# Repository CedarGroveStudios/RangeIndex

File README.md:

# Range_Slicer
## cedargrove_range_slicer
A CircuitPython class for scaling a range of input values into indexed/quantized output values. Adjustable output slice hysteresis is used to provide dead-zone squelching.

[Conceptual Methodology (animation)](https://youtu.be/ndU70NTm_Bk)

Range_Slicer is a general-purpose analog value converter that linearly scales the input then quantizes it into a collection of precise output slice values. The class detects input value changes and applies selectable hysteresis when slice edge thresholds are reached to eliminate dead-zone noise issues. Applications include converting rotary knob position to discrete ranges of MIDI values, analog signal noise processing, level detection, and signal display.

### Implementation Notes

See use example code in the _examples_ folder.

#### Software and Dependencies:
•	Adafruit CircuitPython firmware for the supported boards: https://github.com/adafruit/circuitpython/releases

#### ```class cedargrove_range_slicer.Slicer(*, in_min=0, in_max=65535, out_min=0, out_max=65535, slice=1.0, hyst_factor=0.10, out_integer=False, debug=False)```

Class representing the CedarGroveMaker Range_Slicer.

Parameters:	

-	`in_min` – The input range minimum. Can be any positive or negative value, smaller or larger than the input range maximum. Input range minimum and maximum values cannot be equal. Defaults to `0`.

-	`in_max` – The input range maximum. Can be any positive or negative value, smaller or larger than the input range minimum. Input range minimum and maximum values cannot be equal. Defaults to `65535`.

-	`out_min` – The output index minimum. Can be any positive or negative value, smaller or larger than the output index maximum. Output index minimum and maximum values cannot be equal. Defaults to `0`.

-	`out_max` – The output index maximum. Can be any positive or negative value, smaller or larger than the output index minimum. Output index minimum and maximum values cannot be equal. Defaults to `65535`.

-	`slice` – The size of an output index slice. Can be any positive or negative value other than zero. Defaults to `1.0`.

-	`hyst_factor` – The size of the hysteresis threshold expressed as a factor of the slice size. Can be a positive value from 0 to 1.0. Defaults to `0.10` (10% of the slice size value).

- `out_integer` - Truncates the output value to an integer data type. Defaults to False (floating data type).

-	`debug` – Turn on debug printout. Defaults to `False`.

#### `range_slicer(input=0)`

Applies the slicer algorithm to an input value using the initialization parameters. Returns 1) the output index floating point value (default) or optionally truncated integer value and 2) a flag that is set to `True` when the output value is not equal to the previous result. This is the primary function of the Range_Slicer class.

Parameters:	

- `input` – The input value to convert. Can be any positive or negative numeric value. Defaults to `0`.

#### `range_min(in_min=0)` 

Changes the default range (input) minimum to a new value.

Parameters:	

- `in_min` – The input range minimum. Can be any positive or negative value, smaller or larger than the input range maximum. Input range minimum and maximum values cannot be equal. Defaults to `0`.

#### `range_max(in_max=65535)` 

Changes the default range (input) maximum to a new value.

Parameters:	

- `in_max` – The input range maximum. Can be any positive or negative value, smaller or larger than the input range minimum. Input range minimum and maximum values cannot be equal. Defaults to `65535`.

#### `index_min(out_min=0)` 

Changes the default index (output) minimum to a new value.

Parameters:	

- `out_min` – The index output minimum. Can be any positive or negative value, smaller or larger than the output index maximum. Output index minimum and maximum values cannot be equal. Defaults to `0`.

#### `index_max(out_max=65535)` 

Changes the default index (output) maximum to a new value.

Parameters:	

- `out_max` – The output index maximum. Can be any positive or negative value, smaller or larger than the output index minimum. Output index minimum and maximum values cannot be equal. Defaults to `65535`.

#### `slice(size=1.0)` 

Changes the default slice size to a new value.

Parameters:	

- `size` – The size of an index output slice. Can be any positive or negative value other than zero. Defaults to `1.0`.

#### `hysteresis(hyst_factor=0.10)`

Changes the default hysteresis threshold to a new value.

Parameters:	

- `hyst_factor` – The size of the hysteresis threshold expressed as a factor of the slice size. Can be a positive value from 0 to 1.0. Defaults to `0.10` (10% of the slice size value).

#### `index_type(out_integer=False)`

Changes the default output index value data type from floating to integer.

Parameters:	

- `out_integer` - Truncates the output value to an integer data type. Defaults to False (floating data type).

________________________________________
© Copyright 2019, 2020 Cedar Grove Studios, Revision 3.0.

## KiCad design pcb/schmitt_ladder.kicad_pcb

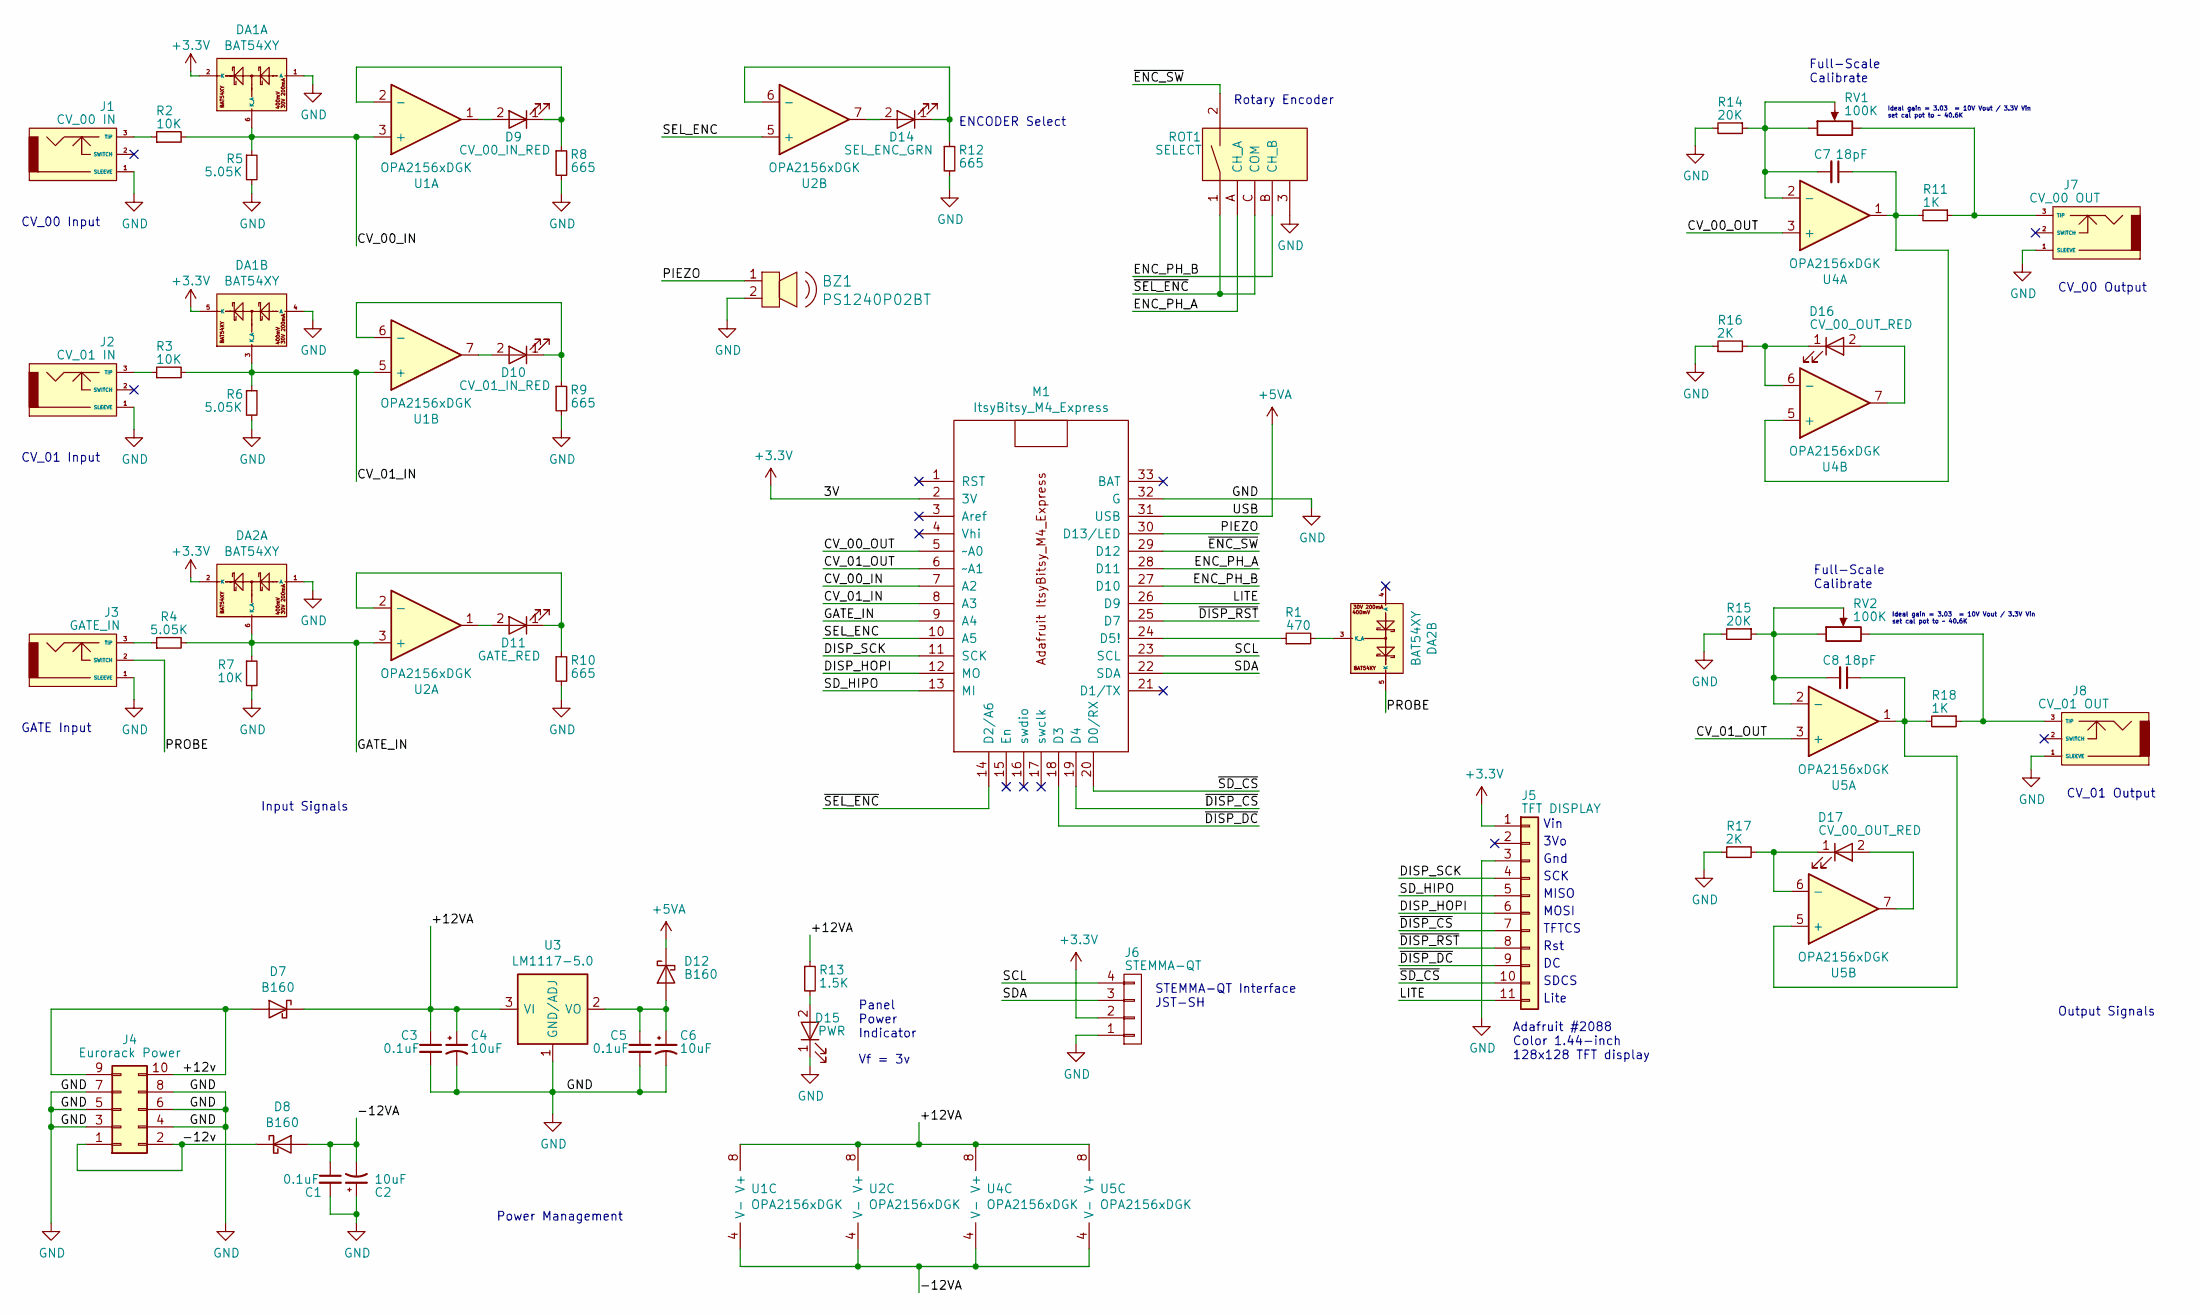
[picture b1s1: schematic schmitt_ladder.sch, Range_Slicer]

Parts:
BZ1: PS1240P02BT; Piezo_Transducer_THT_PS1240P02BT; MPN PS1240P02BT; Digi-Key_PN 445-2525-1-ND
C1, C3, C5: 0.1uF; C_0805_2012Metric
C2, C4, C6: 10uF; C_1210_3225Metric
C7, C8: 18pF; C_0805_2012Metric
D7, D8, D12: B160; D_SMA
D9: CV_00_IN_RED; LED_D3.0mm
D10: CV_01_IN_RED; LED_D3.0mm
D11: GATE_RED; LED_D3.0mm
D14: SEL_ENC_GRN; LED_D3.0mm
D15: PWR; LED_D3.0mm
D16, D17: CV_00_OUT_RED; LED_D3.0mm
DA1, DA2: BAT54XY; SOT-363_SC-70-6
J1: CV_00 IN; Schurter_4832.2211_3.5mm_vert_TS_switch
J2: CV_01 IN; Schurter_4832.2211_3.5mm_vert_TS_switch
J3: GATE_IN; Schurter_4832.2211_3.5mm_vert_TS_switch
J4: Eurorack Power; IDC-Header_2x05_P2.54mm_Vertical
J5: TFT DISPLAY; TFT_Display_1.44in_128x128_PID2088
J6: STEMMA-QT; JST_SH_SM04B-SRSS-TB_1x04-1MP_P1.00mm_Horizontal
J7: CV_00 OUT; Schurter_4832.2211_3.5mm_vert_TS_switch
J8: CV_01 OUT; Schurter_4832.2211_3.5mm_vert_TS_switch
M1: ItsyBitsy_M4_Express; ItsyBitsy M4 Express
R1: 470; R_0805_2012Metric
R2, R3, R7: 10K; R_0805_2012Metric
R4, R5, R6: 5.05K; R_0805_2012Metric
R8, R9, R10, R12: 665; R_0805_2012Metric
R11, R18: 1K; R_0805_2012Metric
R13: 1.5K; R_0805_2012Metric
R14, R15: 20K; R_0805_2012Metric
R16, R17: 2K; R_0805_2012Metric
ROT1: SELECT; Rotary_Encoder_Switched_PEC11R_mntg_hole
RV1, RV2: 100K; Potentiometer_Trimmer_Bourns_PV36W
U1, U2, U4, U5: OPA2156xDGK; VSSOP-8_3.0x3.0mm_P0.65mm
U3: LM1117-5.0; SOT-223-3_TabPin2

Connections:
+3V3: DA1.2 (K), DA1.5 (K), DA2.2 (K), J5.1, J6.2, M1.2 (3V)
+5VA: D12.1 (K), M1.31 (USB)
/+12VA: C3.1, C4.1, D7.1 (K), R13.1, U1.8 (V+), U2.8 (V+), U3.3 (VI), U4.8 (V+), U5.8 (V+)
/+12v: D7.2 (A), J4.9, J4.10
/-12VA: C1.1, C2.2, D8.2 (A), U1.4 (V-), U2.4 (V-), U4.4 (V-), U5.4 (V-)
/-12v: D8.1 (K), J4.1, J4.2
/CV_00_IN: DA1.6 (K_A), M1.7 (A2), R2.2, R5.1, U1.3 (+)
/CV_00_OUT: M1.5 (~~A0), U4.3 (+)
/CV_01_IN: DA1.3 (K_A), M1.8 (A3), R3.2, R6.1, U1.5 (+)
/CV_01_OUT: M1.6 (~~A1), U5.3 (+)
/DISP_HOPI: J5.6, M1.12 (MO)
/DISP_SCK: J5.4, M1.11 (SCK)
/ENC_PH_A: M1.28 (D11), ROT1.A (CH_A)
/ENC_PH_B: M1.27 (D10), ROT1.B (CH_B)
/GATE_IN: DA2.6 (K_A), M1.9 (A4), R4.2, R7.1, U2.3 (+)
/LITE: J5.11, M1.26 (D9)
/PIEZO: BZ1.1, M1.30 (D13/LED)
/PROBE: DA2.5 (K), J3.2 (SWITCH)
/SCL: J6.4, M1.23 (SCL)
/SDA: J6.3, M1.22 (SDA)
/SD_HIPO: J5.5, M1.13 (MI)
/SEL_ENC: M1.10 (A5), U2.5 (+)
/~DISP_CS: J5.7, M1.19 (D4)
/~DISP_DC: J5.9, M1.18 (D3)
/~DISP_RST: J5.8, M1.25 (D7)
/~ENC_SW: M1.29 (D12), ROT1.2
/~SD_CS: J5.10, M1.20 (D0/RX)
/~SEL_ENC: M1.14 (D2/A6), ROT1.1, ROT1.C (COM)
GND: BZ1.2, C1.2, C2.1, C3.2, C4.2, C5.2, C6.2, D15.1 (K), DA1.1 (A), DA1.4 (A), DA2.1 (A), J1.1 (SLEEVE), J2.1 (SLEEVE), J3.1 (SLEEVE), J4.3, J4.4, J4.5, J4.6, J4.7, J4.8, J5.3, J6.1, J7.1 (SLEEVE), J8.1 (SLEEVE), M1.32 (G), R5.2, R6.2, R7.2, R8.2, R9.2, R10.2, R12.2, R14.2, R15.2, R16.1, R17.1, ROT1.3, U3.1 (GND/ADJ)
unnamed: C5.1, C6.1, D12.2 (A), U3.2 (VO)
unnamed: C7.1, R11.2, U4.1, U4.5 (+)
unnamed: C7.2, R14.1, RV1.1, RV1.2, U4.2 (-)
unnamed: C8.1, R18.2, U5.1, U5.5 (+)
unnamed: C8.2, R15.1, RV2.1, RV2.2, U5.2 (-)
unnamed: D9.1 (K), R8.1, U1.2 (-)
unnamed: D9.2 (A), U1.1
unnamed: D10.1 (K), R9.1, U1.6 (-)
unnamed: D10.2 (A), U1.7
unnamed: D11.1 (K), R10.1, U2.2 (-)
unnamed: D11.2 (A), U2.1
unnamed: D14.1 (K), R12.1, U2.6 (-)
unnamed: D14.2 (A), U2.7
unnamed: D15.2 (A), R13.2
unnamed: D16.1 (K), R16.2, U4.6 (-)
unnamed: D16.2 (A), U4.7
unnamed: D17.1 (K), R17.2, U5.6 (-)
unnamed: D17.2 (A), U5.7
unnamed: DA2.3 (K_A), R1.2
unnamed: J1.3 (TIP), R2.1
unnamed: J2.3 (TIP), R3.1
unnamed: J3.3 (TIP), R4.1
unnamed: J7.3 (TIP), R11.1, RV1.3
unnamed: J8.3 (TIP), R18.1, RV2.3
unnamed: M1.24 (D5!), R1.1

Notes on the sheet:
Panel Power Indicator
Full-Scale Calibrate
Ideal gain = 3.03 = 10V Vout / 3.3V Vin set cal pot to ~~ 40.6K
CV_00 Input
Rotary Encoder
STEMMA-QT Interface JST-SH
MISO
SCK
MOSI
Rst
TFTCS
3Vo
Vin
Gnd
Adafruit #2088 Color 1.44-inch 128x128 TFT display
CV_00 Output
Vf = 3v
ENCODER Select
CV_01 Input
GATE Input
Power Management
SDCS
Lite
CV_01 Output
Input Signals
Output Signals

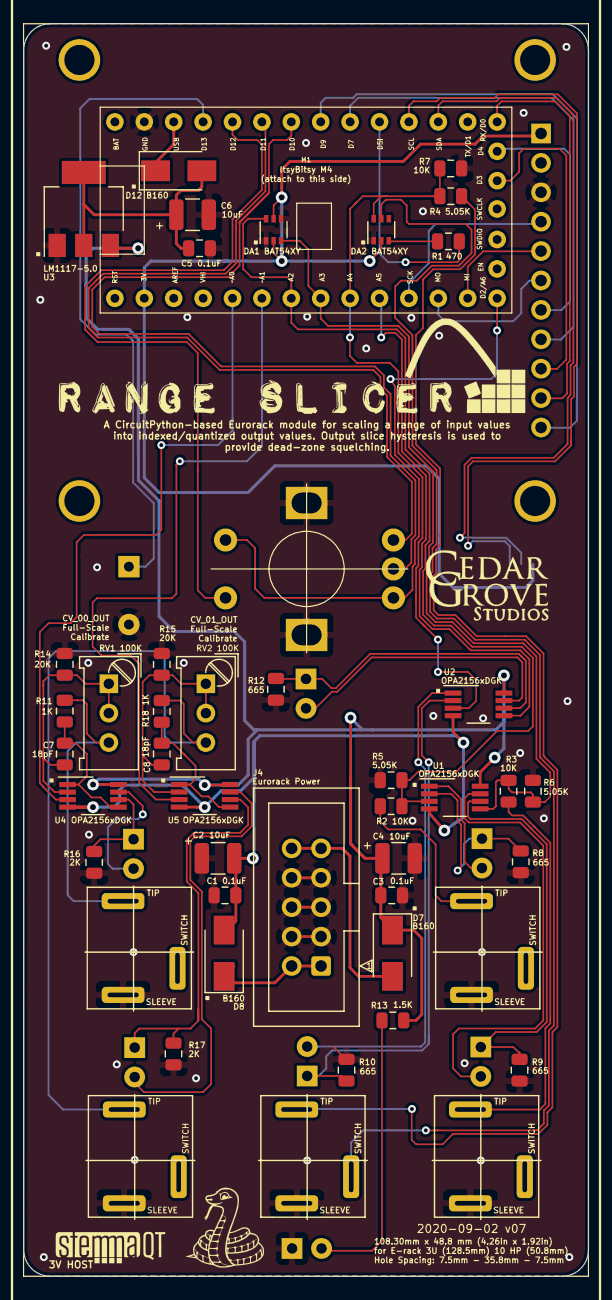
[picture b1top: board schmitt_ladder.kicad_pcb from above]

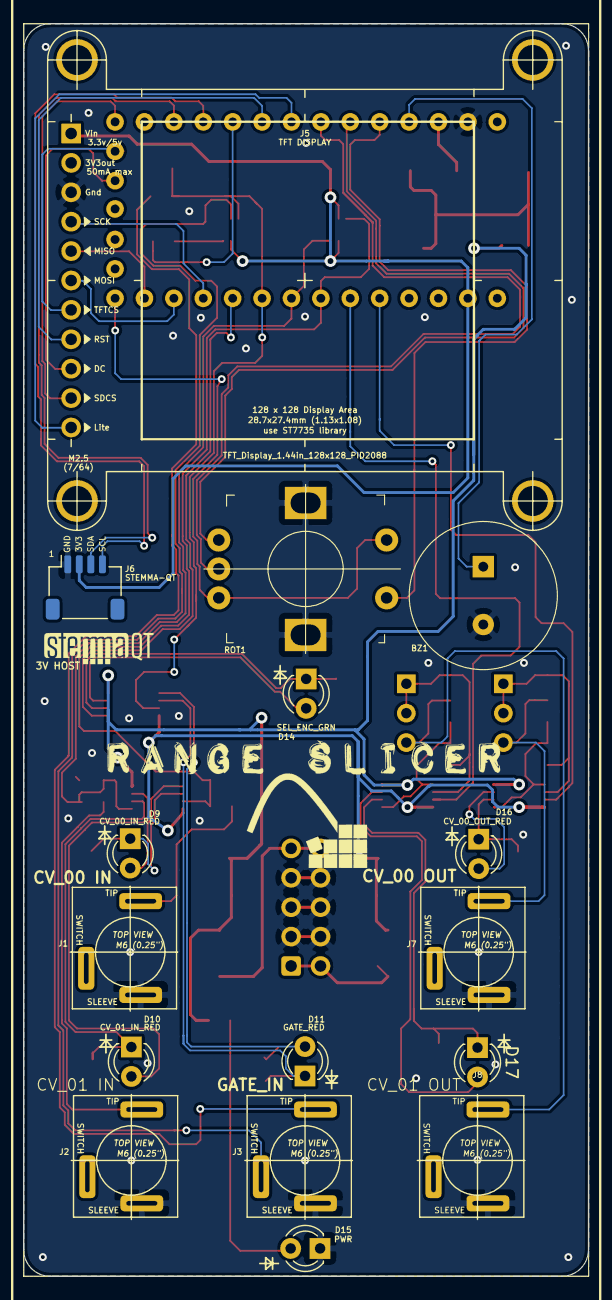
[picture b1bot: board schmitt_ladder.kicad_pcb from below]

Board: 2 copper layers, 48.8 x 108.2 mm, 56 parts (16 on the bottom side), 54 nets.

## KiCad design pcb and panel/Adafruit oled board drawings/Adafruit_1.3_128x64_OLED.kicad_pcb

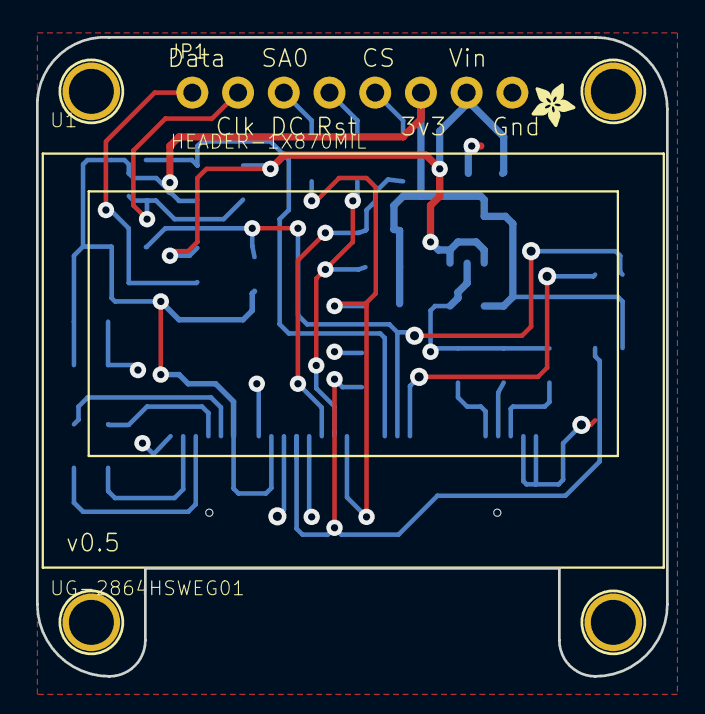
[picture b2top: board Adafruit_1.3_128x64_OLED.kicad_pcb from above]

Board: 2 copper layers, 35.0 x 35.5 mm, 35 parts (0 on the bottom side), 22 nets.

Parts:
C1, C2, C5: 10uF; 0805
C3, C4, C6, C7, C8: 2.2uF; 0805
D1, D2, D3: 1N4148; SOD-323
FID1, FID2: FIDUCIAL; FIDUCIAL_1MM
JP1: HEADER-1X870MIL; 1X08_ROUND_70
Q1, Q2: BSS138; SOT23-WIDE
R2, R4, R5, R6, R11, R12, R13, R14: 10K; 0805
R3: 390K; 0805
SJ1, SJ2: SOLDERJUMPERREFLOW_NOPASTE; SOLDERJUMPER_REFLOW_NOPASTE
U1: UG-2864HSWEG01; UG-2864HSWEG01_1.3_WRAPAROUND
U2: VREG_SOT23-5; SOT23-5
U$23, U$24, U$25, U$26: MOUNTINGHOLE2.5; MOUNTINGHOLE_2.5_PLATED
U$27: ADAFRUIT_2.5MM
U$28: LOGIC_5VREADY_5MM

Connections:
3.3V: C2.1, C6.2, C7.2, JP1.6, Q1.1, Q2.1, R4.2, R5.2, R6.2, R11.2, R12.2, SJ2.1, U1.6, U1.9, U2.5
/CS_3.3V: D1.A, R4.1, U1.13
/CS_5.0V: D1.C, JP1.5
/D0/SCLK/SCK_3.3V: Q2.2, R12.1, U1.18
/D0/SCLK/SCK_5.0V: JP1.2, Q2.3, R14.1
/D1/MOSI/SDA1_3.3V: Q1.2, R11.1, SJ1.1, U1.19
/D1/MOSI/SDA_5.0V: JP1.1, Q1.3, R13.1
/DC/SA0_3.3V: D3.A, R6.1, U1.15
/DC/SA0_5.0V: D3.C, JP1.3
/RST_3.3V: D2.A, R5.1, U1.14
/RST_5.0V: D2.C, JP1.4
GND: C1.2, C2.2, C5.1, C6.1, C7.1, C8.1, JP1.8, R2.1, R3.1, U1.1, U1.8, U1.10, U1.12, U1.29, U1.30, U2.2
unnamed: C3.1, U1.3
unnamed: C3.2, U1.2
unnamed: C4.1, U1.5
unnamed: C4.2, U1.4
unnamed: C5.2, U1.28
unnamed: C8.2, U1.27
unnamed: R2.2, SJ2.2, U1.11
unnamed: R3.2, U1.26
unnamed: SJ1.2, U1.20
VIN: C1.1, JP1.7, R13.2, R14.2, U2.1, U2.3

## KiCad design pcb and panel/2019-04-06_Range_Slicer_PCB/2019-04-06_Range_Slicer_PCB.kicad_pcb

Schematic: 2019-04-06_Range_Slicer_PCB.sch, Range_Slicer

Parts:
C1, C3, C7, C9, C11: 0.1uF; C_0805_HandSoldering
C2: 10uF; C_0805_HandSoldering
C4, C8: 100uF; CP_Elec_8x10.5
C10: 10uF; C_1206_HandSoldering
D1, D2, D3, D4, D5, D6, D7, D8, D9, D10, D11, D12, D13, D14, D15, D21, D23: SD0805S04; D_0805
D16: BLU; LED_D3.0mm
D17, D19: B160; D_SMA
D18: GRN; LED_D3.0mm
D20: GRN; Cedar_Grove_logo_lighted
D22: YEL; LED_D3.0mm
J1: CV IN; Schurter_4832.2211_3.5mm_TS_jack_vert
J2: CV IN MAX; Schurter_4832.2211_3.5mm_TS_jack_vert
J3: CV IN MIN; Schurter_4832.2211_3.5mm_TS_jack_vert
J4: CV HYST; Schurter_4832.2211_3.5mm_TS_jack_vert
J5: CV SLICE; Schurter_4832.2211_3.5mm_TS_jack_vert
J6: CV OUT; Schurter_4832.2211_3.5mm_TS_jack_vert
J7: CV OUT MAX; Schurter_4832.2211_3.5mm_TS_jack_vert
J8: CV OUT MIN; Schurter_4832.2211_3.5mm_TS_jack_vert
J9: OLED DISPLAY; OLED_Display_1.3in_128x64_PID938
J10: STEMMA; JST_PH_B4B-PH-K_04x2.00mm_Straight
J11: Eurorack Power; IDC_Header_Straight_16pins
J12: GATE_IO; Schurter_4832.2211_3.5mm_TS_jack_vert
M1: ItsyBitsy_M4_Express; ItsyBitsy M4 Express
R1, R2, R3, R4, R5, R11, R12, R15, R16, R24: 10K; R_0805_HandSoldering
R6, R7, R8, R9, R10, R13, R14: 5K; R_0805_HandSoldering
R17: 2.03K; R_0805_HandSoldering
R18, R21: 470; R_0805_HandSoldering
R19, R23: 4.7K; R_0805_HandSoldering
R20, R22: 560; R_0805_HandSoldering
ROT1: SELECT; Rotary_Encoder_Switched_PEC11R_mntg_hole
RV1: 10K; Potentiometer_Trimmer_Bourns_PV36W
U1, U5: TLV272
U2: MCP4725A1T-E_CH; SOT-23-6_Handsoldering
U3: LM1117-5.0; SOT-223-3_TabPin2
U4: ‎MCP1804T-A002I/DB; SOT-223-3_TabPin2

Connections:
+3V3: C9.1, C10.1, D1.1 (K), D2.1 (K), D3.1 (K), D4.1 (K), D5.1 (K), D11.1 (K), D12.1 (K), D21.1 (K), J9.7, J10.3, M1.2, R15.1, R16.1, U2.3
+5VA: D17.1 (K), M1.31, R21.1
/3V3: J9.6
/+5VR: C3.1, C4.1, D17.2 (A), U3.2 (VO)
/+5v: J11.11, J11.12
/+12VA: C1.1, C2.1, D19.1 (K), U3.3 (VI), U4.3
/+12v: D19.2 (A), J11.9, J11.10
/-12v: J11.1, J11.2
/CV: J11.13, J11.14
/CV_HYST: D4.2 (A), D9.1 (K), M1.8, R4.2, R9.1
/CV_IN: D1.2 (A), D6.1 (K), M1.5, R1.2, R6.1, U5.3 (+)
/CV_IN_MAX: D2.2 (A), D7.1 (K), M1.6, R2.2, R7.1
/CV_IN_MIN: D3.2 (A), D8.1 (K), M1.7, R3.2, R8.1
/CV_OUT: U1.3 (+), U1.5 (+), U2.1
/CV_OUT_MAX: D11.2 (A), D13.1 (K), M1.14, R11.2, R13.1
/CV_OUT_MIN: D12.2 (A), D14.1 (K), M1.10, R12.2, R14.1
/CV_SLICE: D5.2 (A), D10.1 (K), M1.9, R5.2, R10.1
/GATE_IN: D21.2 (A), D23.1 (K), M1.25, R23.2, R24.1
/Gate: J11.15, J11.16
/OLED_MO: J9.1, M1.12
/OLED_SCK: J9.2, M1.11
/POLL: J1.2, J2.2, J3.2, J4.2, J5.2, J7.2, J8.2, J12.2, R18.2
/SCL: J10.1, M1.23, R16.2, U2.5
/SDA: J10.2, M1.22, R15.2, U2.4
/SELECT_PH_A: M1.28, ROT1.A
/SELECT_PH_B: M1.27, ROT1.B
/~OLED_CS: J9.5, M1.19
/~OLED_DC: J9.3, M1.18
/~OLED_RST: J9.4, M1.26
/~SELECT_EN: M1.30, ROT1.1, ROT1.C
/~SELECT_SW: M1.29, ROT1.2
GND: C1.2, C2.2, C3.2, C4.2, C7.2, C8.2, C9.2, C10.2, C11.2, D6.2 (A), D7.2 (A), D8.2 (A), D9.2 (A), D10.2 (A), D13.2 (A), D14.2 (A), D16.1, D18.1, D20.1, D22.1, D23.2 (A), J1.1, J2.1, J3.1, J4.1, J5.1, J6.1, J7.1, J8.1, J9.8, J10.4, J11.3, J11.4, J11.5, J11.6, J11.7, J11.8, J12.1, M1.32, R6.2, R7.2, R8.2, R9.2, R10.2, R13.2, R14.2, R17.1, R24.2, ROT1.3, U1.4 (V-), U2.2, U2.6, U3.1 (GND/ADJ), U4.2, U5.4 (V-), U5.5 (+)
unnamed: C11.1, R17.2, RV1.1, RV1.2, U1.2 (-)
unnamed: D15.1 (K), R18.1
unnamed: D15.2 (A), M1.24
unnamed: D16.2, R19.2
unnamed: D18.2, R20.2
unnamed: D20.2, R21.2
unnamed: D22.2, R22.2
unnamed: J1.3, R1.1
unnamed: J2.3, R2.1
unnamed: J3.3, R3.1
unnamed: J4.3, R4.1
unnamed: J5.3, R5.1
unnamed: J6.3, RV1.3, U1.1
unnamed: J7.3, R11.1
unnamed: J8.3, R12.1
unnamed: J12.3, R23.1
unnamed: R19.1, U1.6 (-), U1.7
unnamed: R22.1, U5.1, U5.2 (-)
unnamed: U5.6 (-), U5.7
V+: C7.1, C8.1, R20.1, U1.8 (V+), U4.1, U5.8 (V+)

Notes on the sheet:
ItsyBitsy M4 Express
Power Management
Panel Power Indicator
Full-Scale Calibrate
CV Output Ideal gain = 3.03 = 10V Vout / 3.3V Vin set cal pot to ~~ 4.0K
Cedar Grove Logo (PCB)
CV Inputs
Select Rotary Encoder
STEMMA Interface
CV Out
CV In
Data
Clk
DC/SA0
Rst
3v3
Vin
Gnd
Adafruit #938 Monochrome 1.3" 128x64 OLED display
Front Panel Indicators
R17 * C11 = 500usec
C10: Tantalum
(Unused)
Polling Signal Conditioner
CV Output

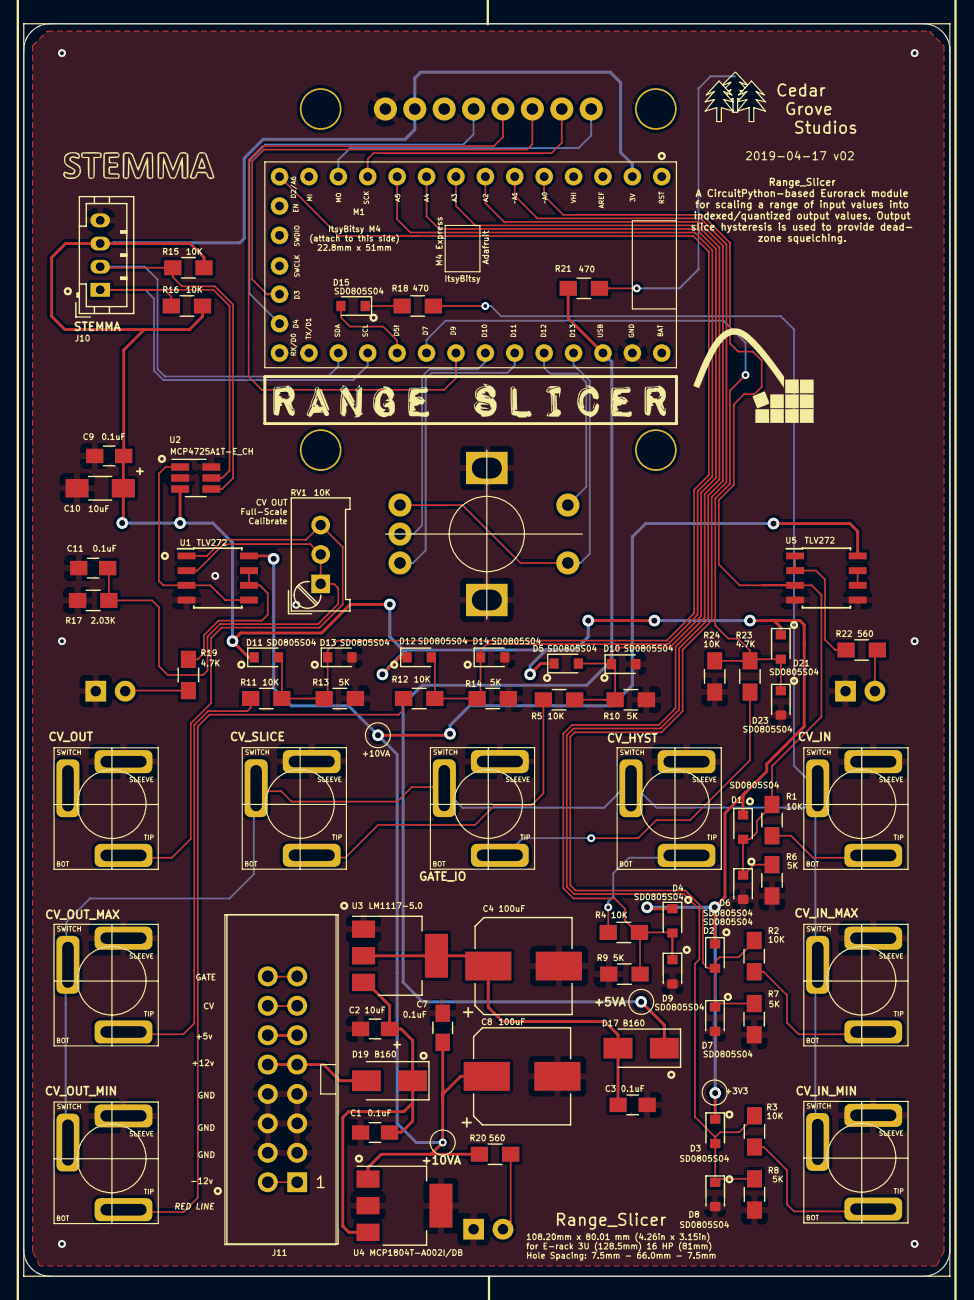
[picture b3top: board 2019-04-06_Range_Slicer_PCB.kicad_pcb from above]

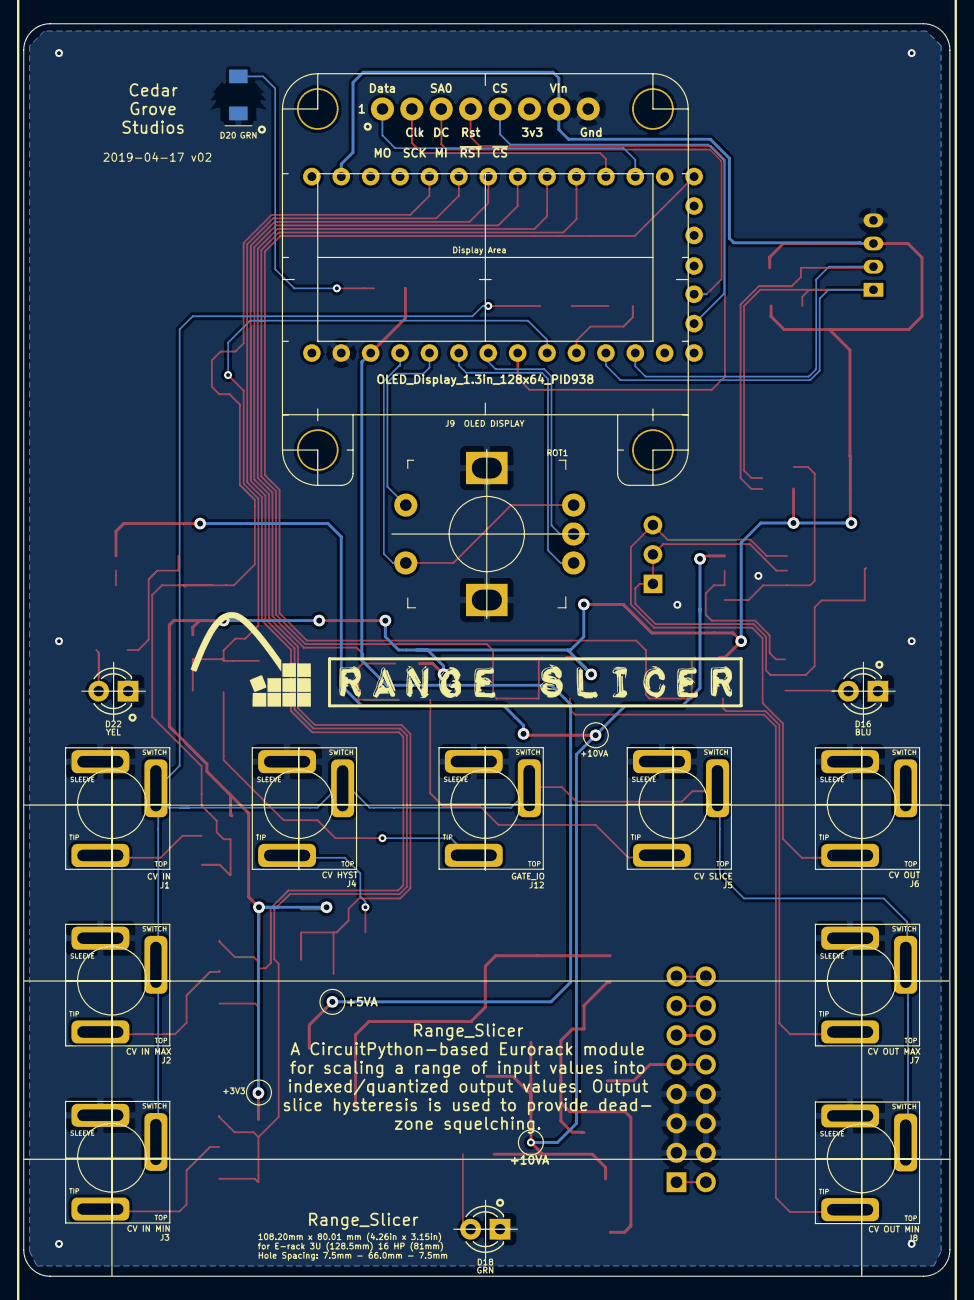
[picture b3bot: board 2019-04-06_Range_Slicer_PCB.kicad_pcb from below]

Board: 2 copper layers, 80.0 x 108.2 mm, 76 parts (14 on the bottom side), 51 nets.

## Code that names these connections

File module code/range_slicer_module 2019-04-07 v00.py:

# range_slicer_module 2019-04-07 v00.py
# --->   works only with CircuitPython 3.1.1   <---
# Range_Slicer PCB 2019-04-06 rev00 with ItsyBitsy M4

import board
import busio as io
import time
import random as ran
import pulseio
import array
from digitalio import DigitalInOut, Direction, Pull
from analogio import AnalogIn, AnalogOut
from simpleio import map_range
import microcontroller as mcu  # for checking CPU temperature
import gc  # for checking memory capacity
import neopixel as neo  # Feather M4
import adafruit_ssd1306
import cedargrove_range_slicer as rs

# ### DEFINE AND INITIALIZE PINS AND DEVICES ###
#  set up and initialize oled display
try:
    spi = io.SPI(board.SCK, MOSI=board.MOSI)
    dc_pin = DigitalInOut(board.D6)
    reset_pin = DigitalInOut(board.D9)
    cs_pin = DigitalInOut(board.D5)
    oled = adafruit_ssd1306.SSD1306_SPI(128, 64, spi, dc_pin, reset_pin, cs_pin)

    oled_connected = True
    print("OLED connected")
except:
    oled_connected = False  # if no i2C connect exception
    print("OLED NOT connected")

if oled_connected:
    screen_pause = 0.0
    oled.fill(0)
    oled.text("Range_Slicer v00", 0, 8)
    oled.show()
    time.sleep(screen_pause)

# dim the on-board RGB LED, yellow indicator
pixel = neo.NeoPixel(board.NEOPIXEL,1, brightness=0.01, auto_write=False)
pixel[0] = (200, 200, 0)
pixel.write()
time.sleep(0.1)

# set up analog inputs
cv_in_pin = AnalogIn(board.A0)
cv_in_max_pin = AnalogIn(board.A1)
cv_in_min_pin = AnalogIn(board.A2)
cv_hyst_pin = AnalogIn(board.A3)
cv_slice_pin = AnalogIn(board.A4)
cv_out_min_pin = AnalogIn(board.A5)
# cv_out_max_pin = AnalogIn(board.A6)  # uncomment for ItsyBitsy

# digital inputs and outputs
sel_ph_a_pin = DigitalInOut(board.D11)
sel_ph_a_pin.direction = Direction.INPUT
sel_ph_a_pin.pull = Pull.UP
sel_ph_b_pin = DigitalInOut(board.D10)
sel_ph_b_pin.direction = Direction.INPUT
sel_ph_b_pin.pull = Pull.UP

sel_sw_pin = DigitalInOut(board.D12)
sel_sw_pin.direction = Direction.INPUT
sel_sw_pin.pull = Pull.UP

rot_en_pin = DigitalInOut(board.D13)
rot_en_pin.direction = Direction.OUTPUT

# poll_pin = DigitalInOut(board.D5)  # uncomment for ItsyBitsy
# poll_pin.direction = Direction.OUTPUT  # uncomment for ItsyBitsy

# ### LISTS AND DICTIONARIES ###

# ### HELPERS ###

def graph_frame():  # draw screen axes and labels
    oled.fill(0)
    oled.line(93,0,93,63,1)
    oled.line(93,2,95,2,1)
    oled.line(32,61,95,61,1)
    oled.line(33,61,33,63,1)
    oled.text(" IN", 0, 0)
    oled.text("max", 0, 9)
    oled.text("min", 0, 27)
    oled.text(" HYS", 0, 45)
    oled.text(" OUT", 97, 0)
    oled.text("max", 97, 9)
    oled.text("min", 97, 27)
    oled.text(" SLC", 97, 45)
    oled.show()

def graph_values(x_min, x_max, y_min, y_max, hys, slc):  # knob values
    oled.text(str(x_max)+".0", 0, 18)
    oled.text(str(x_min)+".0", 0, 36)
    oled.text(str(hys)+"%", 0, 54)
    oled.text(str(y_max)+".0", 97, 18)
    oled.text(str(y_min)+".0", 97, 36)
    oled.text(str(slc)+".0", 97, 54)
    oled.show()

def graph_point(x,y,cross_size):  # current in/out value pointers
    # output axis (y)
    oled.line(93,y,95,y,1)
    oled.line(95,y-1,95,y+1,1)
    # input axis (x)
    oled.line(x,61,x,63,1)
    oled.line(x-1,63,x+1,63,1)
    # crosshair (x,y)
    oled.line(x-cross_size,y,x+cross_size,y,1)
    oled.line(x,y-cross_size,x,y+cross_size,1)

    oled.show()

def graph_in_min_max(x1, x2):  # show min/max and hysteresis lines
    for y in range(4, 62-1, 4):
        oled.line(x1,y,x1+1,y,1)
    for y in range(4, 62-1, 4):
        oled.line(x2,y,x2+1,y,1)
    oled.show()

def graph_out_min_max(y1, y2):  # show output min/max lines
    for x in range(35, 93-1, 4):
        oled.line(x,y1,x+1,y1,1)
    for x in range(35, 93-1, 4):
        oled.line(x,y2,x+1,y2,1)
    oled.show()

def graph_hyst(x_min, x_max, y_min, y_max, hys):  # show hysteresis lines
    oled.line(x_min-hys,y_max,x_max-hys,y_min,1)
    oled.line(x_min+hys,y_max,x_max+hys,y_min,1)
    oled.show()

# ### MAIN CODE SECTION ###

# initialize voice selection index and offset
dsp_voice_idx = 0
dsp_voice_idx_old = 0
dsp_voice_offset = 0

# display system status
gc.collect()  # clean up memory
print("Range_Slicer v00")
print("GC.mem_free:    %0.3f" % float(gc.mem_free()/1000), "KB")
print("CPU.freqency:    %0.1f" % float(mcu.cpu.frequency/1000000), "MHz")
print("CPU.temperature: %0.1f" % mcu.cpu.temperature, "C")
volt_mon = map_range(AnalogIn(board.VOLTAGE_MONITOR).value, 0, 65520, 0, 6.6)
print("Voltage Monitor: %0.1f" % volt_mon, "V")

if oled_connected:
    oled.fill(0)
    oled.text("Range_Slicer v00", 0, 0)
    oled.text("KB free", 56, 10)
    oled.text(str(int(gc.mem_free()/1e2)/10), 8, 10)
    oled.text("MHz", 56, 20)
    oled.text(str(int(mcu.cpu.frequency/1e5)/10), 8, 20)
    oled.text("C", 56, 30)
    oled.text(str(int(mcu.cpu.temperature*10)/10), 16, 30)
    oled.text(str(int(volt_mon*10)/10), 96, 30)
    oled.text("V", 119, 30)
    oled.show()
    time.sleep(screen_pause)

# ### Main Loop ###

graph_frame()


while True:
    x = 64
    y = 32
    x_min = x - 20
    x_max = x + 20
    y_min = y - 20
    y_max = y + 20
    hys = 5
    slc = 1
    cross_size = 3

    graph_values(x_min, x_max, y_min, y_max, hys, slc)
    graph_point(x, y, cross_size)
    graph_in_min_max(x_min, x_max)
    graph_out_min_max(y_min, y_max)
    graph_hyst(x_min, x_max, y_min, y_max, hys)
    time.sleep(1)
    pass

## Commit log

2019-02-09 renamed repository
2019-02-18 initial test code -- still issues with offset calc
2019-02-18 conceptual diagram
2019-02-19 class library beta
2019-02-19 add UI example
2019-02-19 include UI example
2019-02-19 class library beta version
2019-03-05 initial version
    v01
2019-03-05 initial version
2019-03-05 diagram
2019-03-05 range_slicer UI
2019-03-05 Initial Release
2019-03-05 link to youtube concept animation
2019-03-05 added graphical element
2019-03-05 added graphics
2019-03-11 updated parameter names
2019-03-11 latest version (v2.1)
2019-03-11 usage example
2019-03-11 updated to v2.1
2019-03-13 remove
2019-03-13 add joystick and midi_uart code
2019-03-19 update range_slicer library
    include the option to optionally convert the range_slicer output value to integer. Simplifies coding for MIDI applications.
2019-03-21 revert to ladyada's midi libarary
2019-03-22 index change detection update
2019-03-22 updated description
2019-03-22 update to include index value changed flag desc
2019-03-22 update index value output changed flag desc
2019-03-22 add index value changed flag desc
2019-03-25 update example to include out_integer and debug parameters
2019-03-25 update meeblip control code description
2019-04-13 fix .setter tuple issue
2019-04-13 fix .setter issue
2019-04-15 refinements
2019-04-16 further testing of mapper
    works with positive y range only
2019-04-16 Simplify and improve range performance
2019-04-16 cleanup
2019-04-16 remove temp file
2019-04-17 update internal comments; create mpy
2019-04-17 update documents
2019-08-27 remove redundant videos
2019-08-28 reduce size of videos
2019-08-28 remove videos and duplicate photos
2019-08-28 remove unrelated photo
2019-08-28 remove videos
2019-09-04 update graphics
2019-10-17 remove euro module project
2020-01-17 reorganize folders
2020-02-11 update readthedocs
2020-07-16 notify zero range (input) or index (output) span error
2020-09-07 update with index and range input error messages
2020-09-07 update format and error messages
2020-09-08 fix hysteresis recalc issue
2020-09-08 fix hysteresis and offset issue
2020-09-08 fix hysteresis index issue; clean up code
2020-09-08 create version snapshot
2020-09-09 troubleshoot hysteresis issue
2020-09-09 troubleshoot input direction change glitch
2020-09-09 troubleshoot input direction change issue
2020-09-09 troubleshoot input direction glitch issue
2020-09-09 begin update to conceptual model
2020-09-09 implement new core process scheme
2020-09-09 develop new core module
2020-09-10 troubleshoot new algorithm
2020-09-10 proof of concept; need to address offset and inverted spans
2020-09-11 in progress: code cleanup
    to do:
    1) offset ranges
    2) inverted ranges
    3) clean up code for performance
2020-09-12 improve error detection and correction
2020-09-13 try new algorithm
2020-09-13 test latest algorithm
2020-09-14 test new algorithm
2020-09-14 test new algorithm; create schmitt ladder schematic
2020-09-14 test new algorithm; update ladder schematic
2020-09-15 test new algorithm; comment out debug lines
2020-09-15 test of new algorithm; remove debug code
2020-09-16 working on algorithm 4
2020-09-16 test v33
2020-09-17 test of algorithm 4.0
2020-09-17 test algorithm 4.0; first code cleanup pass
2020-09-18 algorithm 4.1 alpha
    remaining issues:
    1) fix output span reversal
    2) fine tune performance
2020-09-21 v4.2 Beta
2020-09-21 3.2 Beta
2020-09-23 4.2 Beta
2020-10-01 update pseudo rtd
2020-10-03 update conceptual diagram
2020-10-03 update conceptual diagrams
2020-10-07 release version 3.0
2020-11-09 update gitignore
